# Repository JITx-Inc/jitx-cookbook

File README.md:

# The JITX Cookbook

Here you'll find a number of recipes (example projects) that will show you what JITX can do while serving as a base for your next project.

### How to Use

1. Install VSCode and JITX extension [How to install JITX](https://docs.jitx.com/faq/installationinstructions.html)
2. Open to root cookbook folder in VSCode with `File -> Open Folder -> (Select jitx-cookbook folder)`
3. Open `main.stanza` in the subfolder of the project that you want to run and press "Ctrl+Enter"

You've now built the recipe! Checkout the tutorial and documentation to learn more about JITX: [JITX Docs](https://docs.jitx.com/)

### Recipes

Click any of the links below to access a detailed walkthrough of how they were designed in JITX.

| Recipe                                                                 | What It Can Do                                                                                                                               |
| -------------                                                          | -------------                                                                                                                                |
| [Battery Charger](./battery_charger_design/)                           | LiPo battery charger, LDO voltage regulator, USB-C connector, JST battery connector, resistors, capacitors, detailed checks, export to KiCad |
| [USB-C Cable Tester](./usb_c_cable_tester/)                            | Test points, programmatic parts placement, USB-C connectors, LEDs, coin cell battery, circuit introspection                                  |
| [BLE-mote Wireless IOT Sensor Board](./ble_mote_esp32_iot_board/)      | Microcontroller, pin assignment (supports/requires), parametric design, design optimization, copper pour, net-classes, stackup               |
| [Hacking Conference Badge](./hacking_conference_badge/)                | A software-defined electronics playground - learn JITX by designing your own conference badge                                                |
| [Example of a reusable regulator design (TPS62933DRLR)](./regulator-example/) | Regulator fed from USB-C PD capable of delivering high current |
| [Example of a reusable keyboard layout generator](./keyboard/) | Keyboard generator which generates layout which is quickly implementable  |
| [Ambiq processor along with a few peripherals](./ambiq_demo/) | System based on Ambiq Apollo 4 Blue processor with wireless charging MIPI-DSI, octal SPI, 6-axis IMU peripherals which demonstrate pin assignment and SI constraints|
### What is a recipe?

These recipes are fully functional projects built in JITX to help show you what JITX can do, teach you how to do what you need in JITX, and to serve as reference or template projects for your next design. Recipes can be thought of as JITX example projects, reference designs, recipes, project blueprints, and/or design templates.

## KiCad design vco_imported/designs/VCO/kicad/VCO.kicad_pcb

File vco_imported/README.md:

# Voltage Controlled Oscillator Recipe

This tutorial guides you on importing a project from KiCad into JITX, modifying it, and exporting it back for production.

## The Project

This is a VCO made for a modular synthesizer in the eurorack standard. The original design is from [here](https://github.com/MatthewATaylor/Modular-Synth-Hardware/tree/main/VCO)

#### General Outline

In this project, we want to:

1. Import an existing KiCad from a GitHub repository
4. Change the board stackup to 4 layers and use JLCPCB rules
2. Change most through hole components to SMD components which are available from LCSC
4. Use a matched PNP transistor pair instead of the 2k tempco resistor with 2 separate PNP transistors
2. Export the design back to KiCad and simulate the output

## Getting Started

#### Prerequisites

To start, we'll need to setup JITX. We can follow this tutorial to get setup: https://docs-testing.jitx.com/faq/installationinstructions.html

Then, we need to clone the repo from which we're importing the design. We'll do this by running:
```
git clone https://github.com/MatthewATaylor/Modular-Synth-Hardware
```

Now we want to create a folder in which we'll have our JITX files. This can be done by using your operating system's file explorer.

#### Importing the design

First, let's open VSCode and make sure that no project is open. If there's a project open then we can start with no project by going to `File -> New Window` or using the keyboard shortcut `Ctrl+Shift+N`.

Next we open the JITX sidebar by clicking the small JITX logo to the side and then clicking "Import from Kicad"

Then we navigate to the folder where we cloned the repo to import from and then to the folder `VCO`. Delete the `Panel` folder or move it somewhere else since we currently don't want to import that project. Now select `VCO` and click `Choose as input directory`.

Select the new folder we made as the output directory. If the import was successful, your VSCode window should look like this:

The files generated are as follows:

```text
.
├── board.stanza                    The definition of the board shape, stackup, and rules
├── components                      Automatically generated component files for each unique component on the board
│   └── UNKNOWN
│       └── ... 
├── geometry.stanza                 The definition of each of the copper-filled layers and traces made previously on the board 
├── labels.stanza                   The silkscreens of components and their location
├── landpatterns                    The landpatterns of automatically generated components
│   └── ...
├── log.txt                         The log containing errors and warnings during the import process
├── placements.stanza               Contains the fixed location at which each component is placed
├── properties.stanza               Contains properties automatically generated for each component
├── reference-designators.stanza    Contains the name of each component as shown on the board
├── run-design.stanza               Helper functions to build, check, and export the design
├── stanza.proj                     Contains the locations of libraries that are imported into the project
├── symbols                         Contains the symbols used for the schematic
│   └── ... 
└── VCO.stanza                      Main file containing the instantiation of components and their connections
```

## Main Design

First, we want to remove the existing trace geometry since we want to make our own using the autorouter. We can do this by removing or commenting out the following line in `VCO.stanza`:
```
add-main-geometry()
```

Let's also define our 4 copper layers, the current stackup is:
```text
==GND==
==+12==
==-12==
==GND==
```
We have +12V and -12V as nets since we're receiving a bipolar power supply.

We also want to increase the size of our power traces so we will make a `NetClass` for that.

Now, we want to change our stackup and rules. We'll go to `board.stanza` and change the stackup to a 4 layer board from JLCPCB which is available in the OCDB.

We want a larger default trace too so we can copy the JLCPCB rules from `ocdb/manufacturers/rules.stanza` and change `min-copper-width` to `0.25`

In `run-design.stanza`, change `export-design()` to `compile-design(main)` so that when we run `ctrl+enter` inside, we can view the board and schematic

#### Replacing passive components

Next, we want to change out our generic components to something available from LCSC which is also an SMD component. We'll move to `VCO.stanza` and switch out our resistors and capacitors. We don't have to explicitly define values for each component and instead we can take the value from the `emodel` (electrical model) of our component. Here we made 2 functions to convert our components with emodels to resistors or capacitors:
```
public defn emodel2resistor (component:Instantiable -- extraparams:Tuple = []) :
  chip-resistor(to-tuple(cat(["resistance" => resistance(emodel?(component) as Resistor) as Double], extraparams)))

public defn emodel2capacitor (component:Instantiable -- extraparams:Tuple = []) :
  ceramic-cap(to-tuple(cat(["capacitance" =>capacitance(emodel?(component) as Capacitor) as Double], extraparams)))
```

Now we can change all the instantiations of resistors with a well written find-and-replace command (`ctrl+h`):
```
Find: VCO/components/UNKNOWN/R(-?[0-9]*)/component
Replace: emodel2resistor(VCO/components/UNKNOWN/R$1/component, extraparams = ["_exist" => ["vendor_part_numbers.lcsc"]])
```
Don't forget to turn on regular expressions using `alt+r`

Since these resistors are not 0 indexed, we have to change the net statements to use p[2] instead of p[0]. This can be done again with find-and-replace.
```
Find: R(-?[0-9]*).p\[0\]
Replace: R$1.p[2]
```

The same can be done with capacitors

Some of our capacitors are better as film capacitors since they are less microphonic and more linear so we will replace those with film capacitors from a database part query
```
public inst jitx-C-3 :  database-part(["mpn" => "ECHU1C102GX5", "manufacturer" => "Panasonic"])
```

#### Replacing other components

Instead of the 2 2n3906 transistors and 2k tempco resistor used, we want to use a matched PNP pair. Thus, we will remove the instantiations in `VCO.stanza` (the tempco is R-64), placements in `placements.stanza`, reference designators in `reference-designators.stanza`, and `ref-labels` and `value-labels` in `labels.stanza`

Then we can instantiate the matched pair (we're using an mmdt3906) using the database part query and change the original 2n3906 pins to mmdt3906 pins. The tempco resistor's net statements should be removed.
```
public inst mmdt3906 : database-part(["mpn" => "MMDT3906", "manufacturer" => "Jiangsu Changjing Electronics Technology Co., Ltd."])
```

Now we can change the rest of the components to part queries. Components can be found using the Component Search available in JITX. This can be found by going to the JITX sidebar and clicking "Explorer".

It's best to find components that have the same or similar pin names as the names don't have to be replaced in the nets. Alternatively, you can change the component definition by clicking on a component definition while holding `ctrl`, and changing the `pcb-component` to a `pcb-module` and use that format. 

Before:
```
public pcb-component component :
  datasheet = "http://www.ti.com/lit/ds/symlink/tl071.pdf"
  pin-properties :
    [pin:Ref | pads:Ref ... | side:Dir | bank:Ref | electrical-type:String]
    [p[0] | p[1] | Right | A | "Output"]
    [p-[0] | p[2] | Left | A | "Input"]
    [p+[0] | p[3] | Left | A | "Input"]
    [p+[1] | p[5] | Left | B | "Input"]
    [p-[1] | p[6] | Left | B | "Input"]
    [p[1] | p[7] | Right | B | "Output"]
    [V- | p[4] | Down | C | "PowerIn"]
    [V+ | p[8] | Up | C | "PowerIn"]

  assign-landpattern(VCO/landpatterns/DIP-8_W762mm_Socket/DIP-8_W762mm_Socket)
  assign-symbols([
    Ref("A") => TL072A
    Ref("B") => TL072B
    Ref("C") => TL072C
  ])
```

After:
```
public pcb-module component :
  port p : pin[2]
  port p- : pin[2]
  port p+ : pin[2]
  pin V-
  pin V+

  val datasheet = "http://www.ti.com/lit/ds/symlink/tl071.pdf"

  inst tl072 : database-part(["mpn" => "TL072CDT", "manufacturer" => "STMicroelectronics"])

  net (p[0] tl072.P_1OUT)
  net (p[1] tl072.P_2OUT)
  net (p-[0] tl072.P_1IN-)
  net (p-[1] tl072.P_2IN-)
  net (p+[0] tl072.P_1IN+)
  net (p+[1] tl072.P_2IN+)
  net (V- tl072.VCC-)
  net (V+ tl072.VCC+)
```

Note that you need to delete the reference designator for this component in `reference-designators.stanza` after doing this or explicitly choosing the instantiation in the `pcb-module` (`self.TL072-1.tl072` for example). The placement is also lost this way.

## Layout + Order

#### Layout
With all our components and connections defined, now we can place our components where we want on the board. Then we can select pads (`shift+click`) or select whole pads (press `a`) and then press `q` to route traces through those pads. We can use vias where necessary by pressing `v` and then dragging from a pad.

If components are out of place, then change the location and orientation in `placements.stanza` or remove their placement and move them by dragging them around. Components can be rotated by pressing `r`. Note that component placements can't be changed if they're explicitly defined.

#### Export to KiCad

Now that we're happy with the layout, we can export the design straight into KiCad.

First, let's go into `helpers.stanza`, set KiCad as our CAD tool, and add a mapping so that the custom LCSC field get's exported with our components:
```
val export-field-mapping = [
  "LCSC" => "LCSC"
  "lcsc" => "LCSC"
  "vendor_part_numbers.lcsc" => "LCSC"
]
defn export-to-cad () :
  set-paper(ANSI-A4)
  set-export-backend(`kicad)
  export-cad(export-field-mapping)
```
Then we build the project with `Ctrl + Enter`, and export with `export-design()` in our REPL (terminal), and a KiCad project is generated in the "CAD" directory.

#### Finishing touches in KiCad 

Let's open up KiCad, open the project, and open the schematic + board viewers. The first thing to do is to click the "Update PCB with changes made to schematic" button in the board view to ensure everything has synced.

Then, change the silkscreen position and add vias as deemed necessary.

A SPICE simulation can also be done in the schematic viewer of KiCad to test the circuit (this requires some setting up).

## Conclusion

We've now successfully imported and redesigned a PCB using JITX. You can use this as a reference project, copying this workflow to design your own systems. To learn more, check out the other recipes in [the JITX Cookbook Recipes repo](https://github.com/JITx-Inc/jitx-cookbook) and read through the [tutorials](https://docs.jitx.com/tutorials/index.html) in the JITX docs.

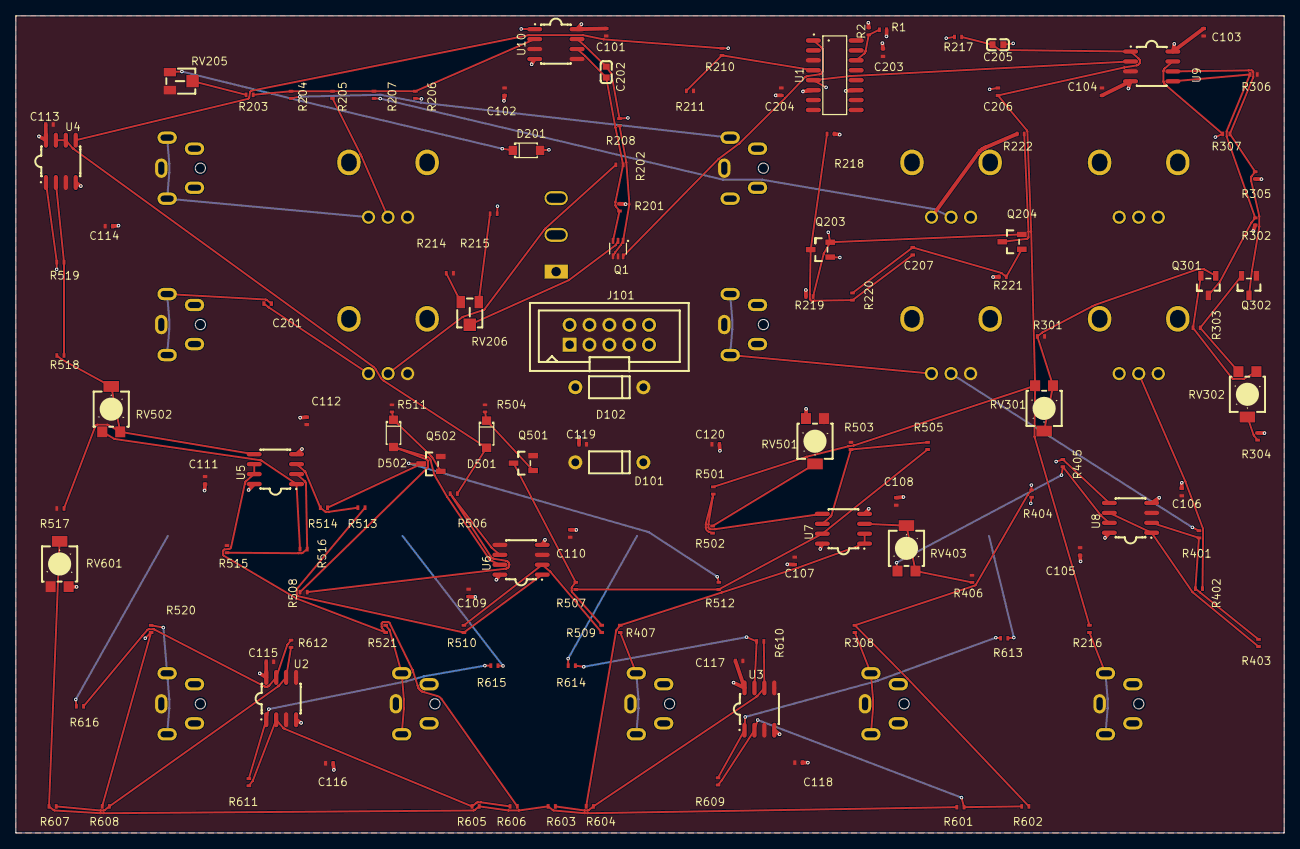
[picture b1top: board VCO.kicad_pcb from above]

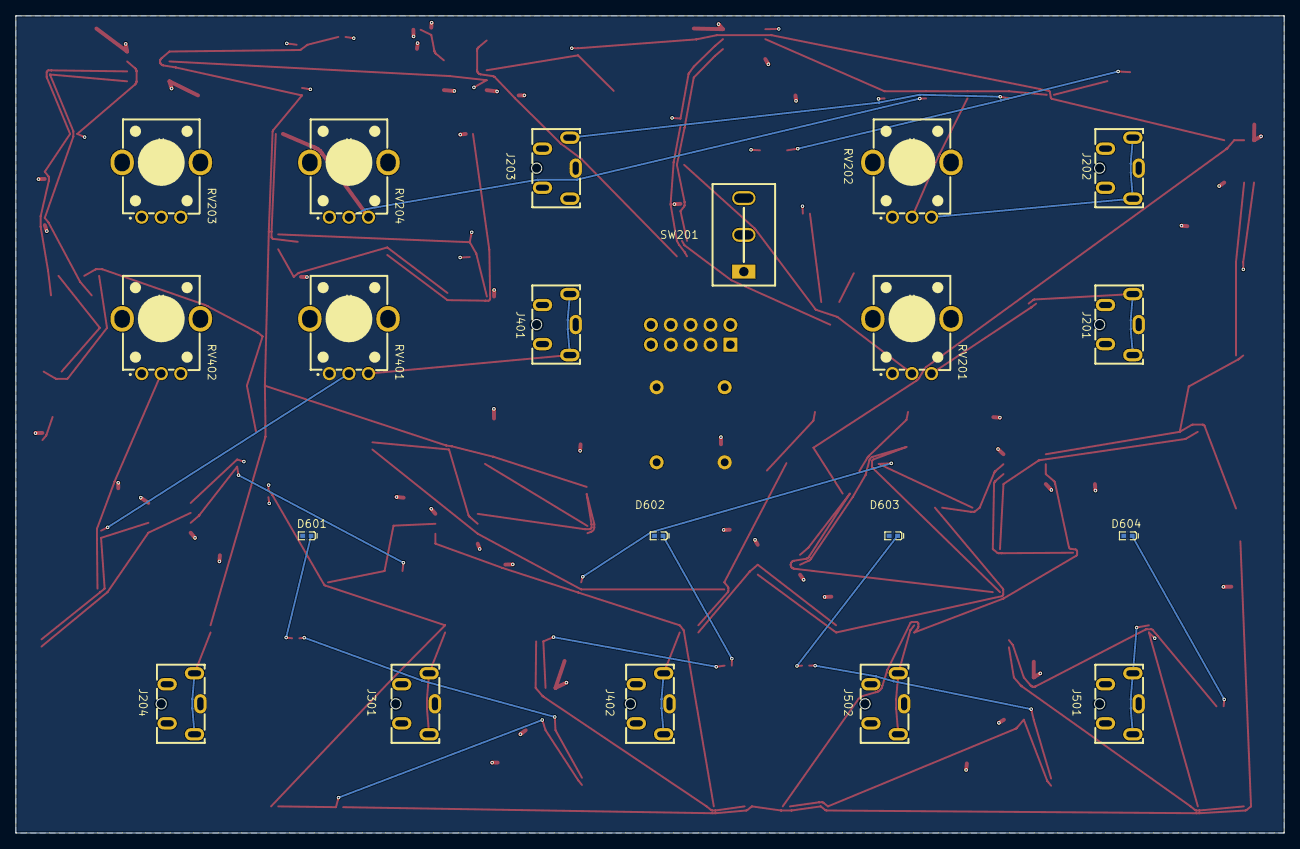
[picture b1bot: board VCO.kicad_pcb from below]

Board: 4 copper layers, 162.2 x 104.5 mm, 151 parts (20 on the bottom side), 87 nets.

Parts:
C101, C102, C103, C104, C105, C106, C107, C108, C109, C110, C111, C112, C113, C114, C115, C116, C117, C118, C203, C204, C206: 10n; Pkg0402_2
C119, C120: 100n; Pkg0402_2
C201: 220n; Pkg0402_2
C202: 1n; C0603_1
C205: 1n; C0603
C207: 47p; Pkg0402_2
D101: 1N5819; DO_41_BD2_4_L4_7_P8_70_D0_9_FD_1
D102: 1N5819; DO_41_BD2_4_L4_7_P8_70_D0_9_FD
D201: 1N4148; SOD_123_L2_7_W1_6_LS3_8_RD
D501: 1N4148; SOD_123_L2_7_W1_6_LS3_8_RD_2
D502: 1N4148; SOD_123_L2_7_W1_6_LS3_8_RD_1
D601: LED; LED0402_RD_3
D602: LED; LED0402_RD_2
D603: LED; LED0402_RD_1
D604: LED; LED0402_RD
J101: Conn_02x05_Odd_Even; IDC_TH_10P_P2_54_V_R2_C5_S2_54
J201: AudioJack2_SwitchT; AUDIO_TH_PJ_3582_B
J202: AudioJack2_SwitchT; AUDIO_TH_PJ_3582_B_5
J203: AudioJack2_SwitchT; AUDIO_TH_PJ_3582_B_2
J204: AudioJack2_SwitchT; AUDIO_TH_PJ_3582_B_7
J301: AudioJack2_SwitchT; AUDIO_TH_PJ_3582_B_3
J401: AudioJack2_SwitchT; AUDIO_TH_PJ_3582_B_8
J402: AudioJack2_SwitchT; AUDIO_TH_PJ_3582_B_4
J501: AudioJack2_SwitchT; AUDIO_TH_PJ_3582_B_1
J502: AudioJack2_SwitchT; AUDIO_TH_PJ_3582_B_6
Q1: MMDT3906; SOT_363_L2_0_W1_3_P0_65_LS2_1_BL
Q203: 2N3904; SOT_23_3_L2_9_W1_3_P1_90_LS2_4_TR
Q204: 2N3904; SOT_23_3_L2_9_W1_3_P1_90_LS2_4_TR_4
Q301: 2N3904; SOT_23_3_L2_9_W1_3_P1_90_LS2_4_TR_3
Q302: 2N3904; SOT_23_3_L2_9_W1_3_P1_90_LS2_4_TR_2
Q501: 2N3904; SOT_23_3_L2_9_W1_3_P1_90_LS2_4_TR_1
Q502: 2N3904; SOT_23_3_L2_9_W1_3_P1_90_LS2_4_TR_5
R1, R2, R211, R302, R305, R517: 10K; Pkg0402
R201: 1M5; Pkg0402
R202, R501, R502, R503, R505: 6K8; Pkg0402
R203: 2M2; Pkg0402_1
R204, R205, R206, R210, R504, R511: 100K; Pkg0402_1
R207: 3M3; Pkg0402
R208, R220: 22K; Pkg0402
R214: 820R; Pkg0402
R215: 47R; Pkg0402_1
R216, R308, R407, R520, R521: 1K; Pkg0402
R217: 1M; Pkg0402
R218: 180K; Pkg0402
R219, R613, R614, R615, R616: 75K; Pkg0402
R221: 560K; Pkg0402
R222: 33K; Pkg0402_1
R301: 220R; Pkg0402
R303: 330R; Pkg0402
R304: 15K; Pkg0402
R306, R307, R506, R508, R509, R510: 7K5; Pkg0402
R401, R403: 150K; Pkg0402
R402: 330K; Pkg0402
R404, R406: 2K2; Pkg0402_1
R405: 2M; Pkg0402
R507, R512: 1K5; Pkg0402_1
R513, R514, R515, R516: 3K9; Pkg0402
R518, R519, R601, R602, R603, R604, R605, R606, R607, R608, R609, R610, R611, R612: 680K; Pkg0402
RV201: 50K; RES_TH_RK09K1130AAU
RV202: 50K; RES_TH_RK09K1130AAU_3
RV203: 50K; RES_TH_RK09K1130AAU_1
RV204: 50K; RES_TH_RK09K1130AAU_4
RV205: 100K; RES_ADJ_SMD_3313J_1_1
RV206: 100R; RES_ADJ_SMD_3313J_1
RV301: 10K; RES_ADJ_SMD_3314G_1_103E_4
RV302: 10K; RES_ADJ_SMD_3314G_1_103E_2
RV401: 50K; RES_TH_RK09K1130AAU_2
RV402: 50K; RES_TH_RK09K1130AAU_5
RV403: 10K; RES_ADJ_SMD_3314G_1_103E
RV501: 10K; RES_ADJ_SMD_3314G_1_103E_3
RV502: 10K; RES_ADJ_SMD_3314G_1_103E_1
RV601: 10K; RES_ADJ_SMD_3314G_1_103E_5
SW201: SW_SPDT; SW_TH_MT_0_103_A101_M200_RS
U1: LM13700MNOPB; SOIC_16_L9_9_W3_9_P1_27_LS6_0_BL
U2, U3, U4, U5, U6, U7, U8, U9, U10: TL072CDT; SOIC_8_L5_0_W4_0_P1_27_LS6_0_BL

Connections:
/2: TL072-8_tl072/Net-J204-PadT: J204.3, J204.6, R216.2
/2: TL072-8_tl072/Net-J301-PadT: J301.3, J301.6, R308.2
/2: TL072-8_tl072/Net-Q301-Pad1: Q301.1 (E), R303.1, RV302.3
/2: TL072-8_tl072/Net-Q301-Pad3: Q301.3 (C), R302.2, R306.2, U9.5 (P_2IN+)
/2: TL072-8_tl072/Net-Q302-Pad1: Q302.1 (E), R303.2, RV302.1
/2: TL072-8_tl072/Net-Q302-Pad3: Q302.3 (C), R305.2, R307.1, U9.6 (P_2IN-)
/2: TL072-8_tl072/Net-R304-Pad1: R304.1, RV302.2
/3: TL072-9_tl072/LEDPulse: R407.2, R604.2, U7.1 (P_1OUT), U7.2 (P_1IN-)
/3: TL072-9_tl072/Net-D201-Pad1: D201.1 (K), RV205.3
/3: TL072-9_tl072/Net-D601-Pad1: D601.1 (K), R613.1
/3: TL072-9_tl072/Net-D602-Pad1: D602.1 (K), R614.1
/3: TL072-9_tl072/Net-J203-PadT: J203.3, J203.6, R204.1
/3: TL072-9_tl072/Net-J402-PadT: J402.3, J402.6, R407.1
/3: TL072-9_tl072/Net-R203-Pad1: R203.1, RV205.2
/3: TL072-9_tl072/Net-R207-Pad1: R207.1, RV204.2
/3: TL072-9_tl072/Net-R502-Pad1: R502.1, RV501.2
/3: TL072-9_tl072/Net-R601-Pad1: R601.1, R602.1, R609.2, U3.2 (P_1IN-)
/3: TL072-9_tl072/Net-R603-Pad1: R603.1, R604.1, R610.2, U3.6 (P_2IN-)
/3: TL072-9_tl072/Net-R609-Pad1: R609.1, R613.2, U3.1 (P_1OUT)
/3: TL072-9_tl072/Net-R610-Pad1: R610.1, R614.2, U3.7 (P_2OUT)
/4: TL072-7_tl072/Net-C207-Pad1: C207.1, Q203.3 (C), R218.2, R220.1
/4: TL072-7_tl072/Net-C207-Pad2: C207.2, Q204.2 (B), R220.2, R221.1
/4: TL072-7_tl072/Net-D501-Pad1: D501.1 (K), Q501.2 (B), R504.2
/4: TL072-7_tl072/Net-D603-Pad1: D603.1 (K), R615.1
/4: TL072-7_tl072/Net-D604-Pad1: D604.1 (K), R616.1
/4: TL072-7_tl072/Net-J502-PadT: J502.3, J502.6, R521.1
/4: TL072-7_tl072/Net-Q203-Pad2: Q203.2 (B), R217.2
/4: TL072-7_tl072/Net-Q204-Pad3: Q204.3 (C), R222.2
/4: TL072-7_tl072/Net-R206-Pad1: R206.1, RV203.2
/4: TL072-7_tl072/Net-R402-Pad1: R402.1, RV402.2
/4: TL072-7_tl072/Net-R403-Pad2: R403.2, U8.1 (P_1OUT), U8.6 (P_2IN-)
/4: TL072-7_tl072/Net-R405-Pad2: R405.2, RV403.3, U8.7 (P_2OUT)
/4: TL072-7_tl072/Net-R605-Pad1: R605.1, R606.1, R611.2, U2.2 (P_1IN-)
/4: TL072-7_tl072/Net-R607-Pad1: R607.1, R608.1, R612.2, U2.6 (P_2IN-)
/4: TL072-7_tl072/Net-R611-Pad1: R611.1, R615.2, U2.1 (P_1OUT)
/4: TL072-7_tl072/Net-R612-Pad1: R612.1, R616.2, U2.7 (P_2OUT)
/5: TL072-4_tl072/Net-D502-Pad1: D502.1 (K), Q502.2 (B), R511.2
/5: TL072-4_tl072/Net-D502-Pad2: D502.2 (A), R508.2, U6.7 (P_2OUT)
/5: TL072-4_tl072/Net-J401-PadT: J401.3, J401.6, RV401.3
/5: TL072-4_tl072/Net-J501-PadT: J501.3, J501.6, R520.1
/5: TL072-4_tl072/Net-Q502-Pad3: Q502.3 (C), R512.1, R514.1
/5: TL072-4_tl072/Net-R401-Pad1: R401.1, RV401.2
/5: TL072-4_tl072/Net-R506-Pad2: R506.2, R508.1, U6.6 (P_2IN-)
/5: TL072-4_tl072/Net-R509-Pad2: R509.2, R510.1, U6.2 (P_1IN-)
/5: TL072-4_tl072/Net-R510-Pad2: R510.2, R513.1, U6.1 (P_1OUT)
/5: TL072-4_tl072/Net-R513-Pad2: R513.2, R514.2, U5.3 (P_1IN+)
/5: TL072-4_tl072/Net-R515-Pad2: R515.2, R516.1, U5.2 (P_1IN-)
/5: TL072-4_tl072/Net-R516-Pad2: R516.2, RV502.3, U5.1 (P_1OUT)
/5: TL072-4_tl072/Net-R517-Pad2: R517.2, R518.2, RV502.1, RV502.2, U5.5 (P_2IN+)
/5: TL072-4_tl072/Net-R518-Pad1: R518.1, R519.2, U4.2 (P_1IN-)
/6: CA3080_lm13700/Net-C201-Pad1: C201.1, J201.3, J201.6
/6: CA3080_lm13700/Net-C201-Pad2: C201.2, RV201.3
/6: CA3080_lm13700/Net-C205-Pad1: C205.1, SW201.1
/6: CA3080_lm13700/Net-C206-Pad1: C206.1, SW201.3
/6: CA3080_lm13700/Net-J202-PadT: J202.3, J202.6, RV202.3
/6: CA3080_lm13700/Net-R202-Pad1: R202.1, RV201.2
/6: CA3080_lm13700/Net-R205-Pad1: R205.1, RV202.2
/6: CA3080_lm13700/Net-R210-Pad2: R210.2, R211.1, U1.4 (Input-0)
/7: R_Potentiometer_Trim-7/Net-R214-Pad1: R214.1, RV206.1
/7: R_Potentiometer_Trim-7/Net-R215-Pad2: R215.2, RV206.3
BaseSquare: Q203.1 (E), Q204.1 (E), R210.1, R219.1, U4.5 (P_2IN+)
BaseTriangle: C205.2, C206.2, R216.1, R217.1, R501.1, RV301.1, U9.1 (P_1OUT)
GND: C101.2, C102.2, C103.2, C104.2, C105.2, C106.2, C107.2, C108.2, C109.2, C110.2, C111.2, C112.2, C113.2, C114.2, C115.2, C116.2, C117.2, C118.2, C119.2, C120.1, C203.2, C204.2, D101.1 (A), D102.2 (K), D601.2 (A), D602.2 (A), D603.2 (A), D604.2 (A), J101.3, J101.4, J101.5, J101.6, J101.7, J101.8, J201.2, J202.2, J203.2, J204.2, J301.2, J401.2, J402.2, J501.2, J502.2, Q1.5 (B2), Q302.2 (B), Q501.1 (E), Q502.1 (E), R211.2, R214.2, R301.2, R306.1, R406.1, R503.1, R504.1, R511.1, R515.1, R517.1, RV201.1, RV202.1, RV205.1, RV401.1, RV501.3, RV601.3, U1.3 (Input+0), U2.3 (P_1IN+), U2.5 (P_2IN+), U3.3 (P_1IN+), U3.5 (P_2IN+), U4.3 (P_1IN+), U6.3 (P_1IN+), U6.5 (P_2IN+), U8.3 (P_1IN+), U9.3 (P_1IN+), U10.3 (P_1IN+), U10.5 (P_2IN+)
LEDInvertedSaw: R519.1, R520.2, R608.2, U4.1 (P_1OUT)
LEDSaw: R521.2, R606.2, U5.6 (P_2IN-), U5.7 (P_2OUT)
LEDSine: R307.2, R308.1, R404.2, R602.2, U9.7 (P_2OUT)
Net+12V: C101.1, C103.1, C105.1, C107.1, C109.1, C111.1, C113.1, C115.1, C117.1, C119.1, C203.1, D101.2 (K), J101.1, J101.2, R1.1, R218.1, R222.1, R302.1, R305.1, RV203.3, RV204.3, RV402.3, RV501.1, RV601.1, U1.11 (V+), U2.8 (VCC+), U3.8 (VCC+), U4.8 (VCC+), U5.8 (VCC+), U6.8 (VCC+), U7.8 (VCC+), U8.8 (VCC+), U9.8 (VCC+), U10.8 (VCC+)
Net-12V: C102.1, C104.1, C106.1, C108.1, C110.1, C112.1, C114.1, C116.1, C118.1, C120.2, C204.1, D102.1 (A), J101.9, J101.10, R2.2, R201.1, R219.2, R221.2, R304.2, RV203.1, RV204.1, RV402.1, U1.6 (V-), U2.4 (VCC-), U3.4 (VCC-), U4.4 (VCC-), U5.4 (VCC-), U6.4 (VCC-), U7.4 (VCC-), U8.4 (VCC-), U9.4 (VCC-), U10.4 (VCC-)
unnamed: R1.2, R2.1, U1.14 (Input+1)
Net-C202-Pad1: C202.1, Q1.3 (C2), R201.2, R202.2, U10.6 (P_2IN-)
Net-C202-Pad2: C202.2, D201.2 (A), R208.2, U10.7 (P_2OUT)
Net-D501-Pad2: D501.2 (A), R506.1, U4.6 (P_2IN-), U4.7 (P_2OUT)
Net-Q201-Pad1: Q1.1 (E1), Q1.4 (E2), R208.1
Net-Q202-Pad2: Q1.2 (B1), RV206.2
Net-Q202-Pad3: Q1.6 (C1), U1.1 (Amp_bias_input0)
Net-Q301-Pad2: Q301.2 (B), R301.1, RV301.2, RV301.3
Net-Q501-Pad3: Q501.3 (C), R507.1, R509.1
Net-R203-Pad2: R203.2, R204.2, R205.2, R206.2, R207.2, U10.2 (P_1IN-)
Net-R209-Pad2: R215.1, U10.1 (P_1OUT)
Net-R401-Pad2: R401.2, R402.2, R403.1, U8.2 (P_1IN-)
Net-R404-Pad1: R404.1, R405.1, U8.5 (P_2IN+)
Net-R406-Pad2: R406.2, RV403.1, RV403.2, U7.3 (P_1IN+)
Net-R501-Pad2: R501.2, R502.2, U7.5 (P_2IN+)
Net-R503-Pad2: R503.2, R505.1, U7.6 (P_2IN-)
Net-R505-Pad2: R505.2, R507.2, R512.2, U7.7 (P_2OUT)
Net-R601-Pad2: R601.2, R603.2, R605.2, R607.2, RV601.2
Net-SW201-Pad2: SW201.2, U1.5 (Output0), U9.2 (P_1IN-)

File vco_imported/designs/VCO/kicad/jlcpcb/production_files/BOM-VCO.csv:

Comment,Designator,Footprint,LCSC
100R,RV206,RES_ADJ_SMD_3313J_1,C124614
LED,"D601,D602,D603,D604",LED0402_RD_3,C130719
LM13700MNOPB,U1,SOIC_16_L9_9_W3_9_P1_27_LS6_0_BL,C1346265
220n,C201,Pkg0402_2,C16772
1n,"C202,C205",C0603_1,C178413
SW_SPDT,SW201,SW_TH_MT_0_103_A101_M200_RS,C1788493
2N3904,"Q203,Q204,Q301,Q302,Q501,Q502",SOT_23_3_L2_9_W1_3_P1_90_LS2_4_TR,C18536
2K2,"R404,R406",Pkg0402_1,C1857667
MMDT3906,Q1,SOT_363_L2_0_W1_3_P0_65_LS2_1_BL,C20534
100K,"R204,R205,R206,R210,R504,R511",Pkg0402_1,C2075193
2M2,R203,Pkg0402_1,C2076597
1M5,R201,Pkg0402,C2082545
1M,R217,Pkg0402,C2085938
3K9,"R513,R514,R515,R516",Pkg0402,C2086763
330R,R303,Pkg0402,C2097621
100n,"C119,C120",Pkg0402_2,C2168180
1N5819,"D101,D102",DO_41_BD2_4_L4_7_P8_70_D0_9_FD_1,C2474
10K,"R1,R2,R211,R302,R305,R517",Pkg0402,C2838653
10n,"C101,C102,C103,C104,C105,C106,C107,C108,C109,C110,C111,C112,C113,C114,C115,C116,C117,C118,C203,C204,C206",Pkg0402_2,C318577
1K,"R216,R308,R407,R520,R521",Pkg0402,C3972394
560K,R221,Pkg0402,C3999808
820R,R214,Pkg0402,C4062103
22K,"R208,R220",Pkg0402,C4062114
680K,"R518,R519,R601,R602,R603,R604,R605,R606,R607,R608,R609,R610,R611,R612",Pkg0402,C4075524
180K,R218,Pkg0402,C4078042
3M3,R207,Pkg0402,C4080317
6K8,"R202,R501,R502,R503,R505",Pkg0402,C4156192
7K5,"R306,R307,R506,R508,R509,R510",Pkg0402,C4156241
2M,R405,Pkg0402,C4156295
220R,R301,Pkg0402,C4165539
75K,"R219,R613,R614,R615,R616",Pkg0402,C4266729
1K5,"R507,R512",Pkg0402_1,C4268869
150K,"R401,R403",Pkg0402,C4288097
Conn_02x05_Odd_Even,J101,IDC_TH_10P_P2_54_V_R2_C5_S2_54,C429962
330K,R402,Pkg0402,C4333841
50K,"RV201,RV202,RV203,RV204,RV401,RV402",RES_TH_RK09K1130AAU,C470291
AudioJack2_SwitchT,"J201,J202,J203,J204,J301,J401,J402,J501,J502",AUDIO_TH_PJ_3582_B,C500090
15K,R304,Pkg0402,C593362
TL072CDT,"U10,U2,U3,U4,U5,U6,U7,U8,U9",SOIC_8_L5_0_W4_0_P1_27_LS6_0_BL,C6961
10K,"RV301,RV302,RV403,RV501,RV502,RV601",RES_ADJ_SMD_3314G_1_103E_4,C780220
47R,R215,Pkg0402_1,C852803
33K,R222,Pkg0402_1,C853915
47p,C207,Pkg0402_2,C882562
100K,RV205,RES_ADJ_SMD_3313J_1_1,C89235
1N4148,"D201,D501,D502",SOD_123_L2_7_W1_6_LS3_8_RD,C909967

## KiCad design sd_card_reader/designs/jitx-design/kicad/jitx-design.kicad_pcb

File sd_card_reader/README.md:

# SD Card Reader Cookbook Recipe
This tutorial guides you on creating an SD Card Reader using JITX while highlighting different features that can be used to aid users on their designs.

##  The Project
This is an SD card reader built in a small form factor, designed to fit in the framework laptop (untested).

## Getting Started
#### Prerequisites
To start, we'll need to setup JITX. We can follow this tutorial to get setup: https://docs-testing.jitx.com/faq/installationinstructions.html

Then, we need to create a new project. So let's run VSCode, select the JITX extension, and click "New Project".

Now we're ready to start designing the board.

> NOTE: The code below is not the entire design. Refer to the [Github repo](https://github.com/JITx-Inc/jitx-cookbook/tree/main/sd_card_reader) for a full working design. Below, we describe the design flow and thought process behind designing this board.

#### Intended Functionality
We want our design to be able to:

* Read and write from an SD Card
* Interface with a computer using a USB-C male connector
* Show the status of data transfer with an LED
* Enable USB device customization using an EEPROM
#### Implementation Plan
To accomplish this, we will use:

* A controller: Microchip USB2240-AEZG-06
* A power regulator: ROHM Semicon BD433M5FP-CE2
* An EEPROM: ST Microelectronics M24C04-WMN6TP
* A USB C male connector: HRO Electronics TYPE-C-31-G-03 
* An SD card connector: XUNPU SD-101 
* Miscellaneous generic components

## Components
Most of our main components (like our controller) don't exist in the OCDB so we will define these ourselves. Fortunately, we don't have to build the landpattern definitions and pin definitions as our parts exist in the parts database. 

We can look for parts using the component search. Since, we want to manufacture this board from JLCPCB, we should look for components that have the property `vendor_part_numbers.lcsc`.

We want to define each of our main components in their own separate modules so we can reuse them later on for different projects. Thus, each component is put into a `pcb-module`.

#### Microcontroller
For this project, we're going to use a Microchip USB2240. For each module we're going to follow a workflow:

* See what inputs and outputs we want and define them as pins and ports. 
    * We want to use bundles (ports) for pins that are commonly connected together. We can look for bundles in the OCDB by opening `ocdb/utils/bundles.stanza` 
```
port power : power
port i2c : i2c
port usb-in : usb-2
port sd-card-conn : sd-card-uhs-1-connector
pin LED
```
* We can also create our own bundles if they don't exist in the OCDB. `sd-card-uhs-1-connector` is an example
```
public pcb-bundle sd-card-uhs-1-connector:
  pin CMD ; Command/Response
  port power : power ; 3.3v and 2 ground pins
  pin CLK ; Clock
  port DAT : pin[4] ; Data pins (last pin also used as card detect)
  pin CD ; Card detect
  pin WP ; Write protect
```

* Instantiate the exact part we want using a database part query
    * An alternative to making a query could be searching for this part in the component search and clicking "Create component" after selecting a suitable component.
```
inst usb2240 : database-part(["manufacturer" => "Microchip", "mpn" => "USB2240-AEZG-06"])
```

* Go through the pins using the design explorer (you can find this by opening the sidebar and clicking "Explorer" under the "Views" section)
* Define each pin's properties with the help of the part's datasheet and the [JITX documentation](https://docs.jitx.com/reference/utilities/properties.html)
* Create and connect components that would be consistent for every use case for this design (pull-up resistors and decoupling capacitors etc.)
    * For this design, we always need a 24MHz crystal so we define it with the same workflow
    * `bypass-cap-strap` creates a capacitor which uses `short-trace`. The `short-trace` is a hint to the layout that we want our PCB trace to be as short as possible between both pads
    * It's best to define pins we're not using as a `no-connect` to avoid ERC errors in the design flow
    * The parameter `"_exist" => ["vendor_part_numbers.lcsc"]` allows us to specify that we require the part to have an LCSC number 

#### USB C male connector
Our application uses USB2 so we want to use the USB2 protocol over the USB-C connection. One key aspect of the backwards compatibility is to indicate device type using resistors on the CC1, CC2 pins. In this case, we need a pull-down resistor on the CC1 pin.

## Bundles
Bundles allow us to define a set of pins which are commonly used together and allow us to view the design at a higher level. Bundles also make connecting pins easy and foolproof. For example, we can create a bundle called `sd-card-uhs-1-connector` and define every pin required for an SD card. Now we can use this to connect our controller to the SD Card connector within a single `net` statement.

We can create bundles within bundles too to further simplify our code.

## Main Design 

We want to define a custom shape for our board with 5mm x 2mm notches so we create the board using a Polygon shape:
```
val board-shape = Polygon([Point(-15.0,-15.0), Point(10.0,-15.0), Point(10.0,-13.0), Point(15.0,-13.0), Point(15.0, 13.0), Point(10.0, 13.0), Point(10.0, 15.0), Point(-15.0,15.0)])
```

We also can to use this same shape for our ground copper ground planes which extend from edge to edge.
```
geom(gnd) :
    copper-pour(LayerIndex(0), isolate = 0.1, rank = 1, orphans = true) = board-shape
    copper-pour(LayerIndex(1), isolate = 0.1, rank = 1, orphans = true) = board-shape
```

Now that all our components and the board are defined, we can move on to placing and connecting our modules together. We use the `dims` function to get the dimensions of our custom board shape and use it for placement. 
```
val d = dims(board-shape)
```

Now we instantiate all our modules and also create testpoints which would allow us to update information on our EEPROM.
```
inst logo : ocdb/artwork/jitx-logo/logo(5.0)

; Call all our modules
inst usb : usb-2-on-usb-c-male
place(usb) at loc(x(d) / 2.0 + 1.1, 0.0, -270.0) on Bottom

inst reg : voltage-regulator

inst eeprom : eeprom

val testpoints = add-testpoint([eeprom.power.vdd eeprom.power.gnd eeprom.i2c.sda eeprom.i2c.scl], Testpoint-SMDPad)

inst media-controller : media-controller
place(media-controller) at loc(0.0, 0.0, 0.0) on Top

inst sd-connector : sd-connector
place(sd-connector) at loc(-5.0, 0.0, 270.0) on Bottom
```

We're reusing the LED circuit generator used in the [USB C cable tester](https://github.com/JITx-Inc/jitx-cookbook/tree/main/usb_c_cable_tester) to create our status LED. 
```
inst status-led : components/LED-maker-ROYGB/module(components/LED-maker-ROYGB/RED, property(vdd33.voltage))
```

Connecting our ports is easy now since we can net whole bundles together.
```
net (usb.usb-2.vbus reg.power-in)
net (usb.usb-2 media-controller.usb-in)

net (reg.power-out media-controller.power eeprom.power)

net (media-controller.i2c eeprom.i2c)
net (media-controller.sd-card-conn sd-connector.conn)

net (media-controller.LED status-led.in)
net (status-led.out gnd)
```

`check-design` allows us to use checks already made in the OCDB and use it for our board. 

## Layout + Order

#### Layout

With all our components and connections defined, now we can place our components where we want on the board. Then we can select single pads (`click`), extend the selection of pads (`shift+click`) or select all pads connected to the pad we first selected (press `a`) and then press `q` to route traces through those pads.

#### Export to KiCad

Now that we're happy with the layout, we can export the design straight into KiCad.

First, let's go into `helpers.stanza`, set KiCad as our CAD tool, and add a mapping so that the custom LCSC field gets exported as a component property:
```
val export-field-mapping = [
  "LCSC" => "LCSC"
  "lcsc" => "LCSC"
  "vendor_part_numbers.lcsc" => "LCSC"
]
defn export-to-cad () :
  set-paper(ANSI-A4)
  set-export-backend(`kicad)
  export-cad(export-field-mapping)
```
Then we build the project with `Ctrl + Enter`, and export with `export-design()` in our REPL (terminal), and a KiCad project is generated in the "CAD" directory.

#### Finishing touches in KiCad 

Let's open up KiCad, open the project, and open the schematic + board viewers. The first thing to do is to click the "Update PCB with changes made to schematic" button in the board view to ensure everything has synced.

Then we need to change the reference texts' silkscreen location as necessary.

#### Export from Kicad, order from JLCPCB

Install [this](https://github.com/Bouni/kicad-jlcpcb-tools) plugin in Kicad to manage your components from LCSC and generate your Gerbers, BOM, and CPL. 

Upload your design to JLCPCB and order it:

## Conclusion

We've now successfully designed a PCB using JITX. You can use this as a reference project, copying this workflow to design your own systems. To learn more, check out the other recipes in [the JITX Cookbook Recipes repo](https://github.com/JITx-Inc/jitx-cookbook) and read through the [tutorials](https://docs.jitx.com/tutorials/index.html) in the JITX docs.

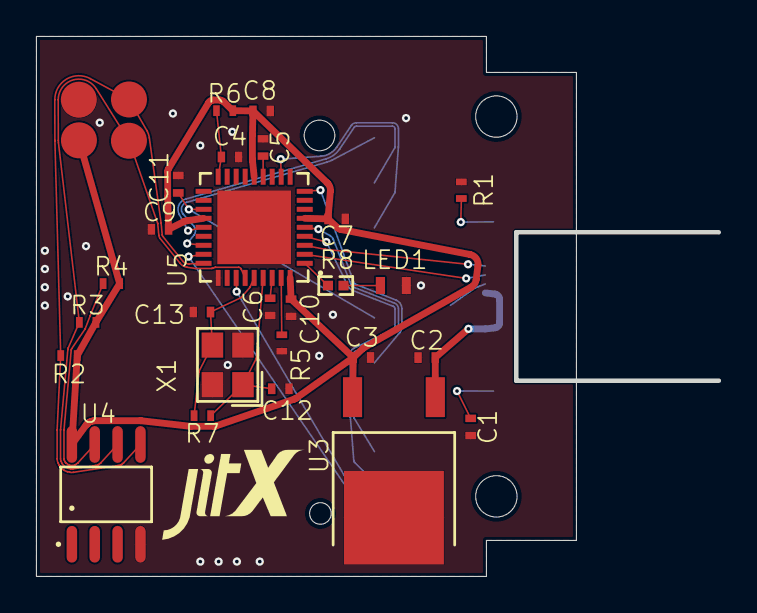
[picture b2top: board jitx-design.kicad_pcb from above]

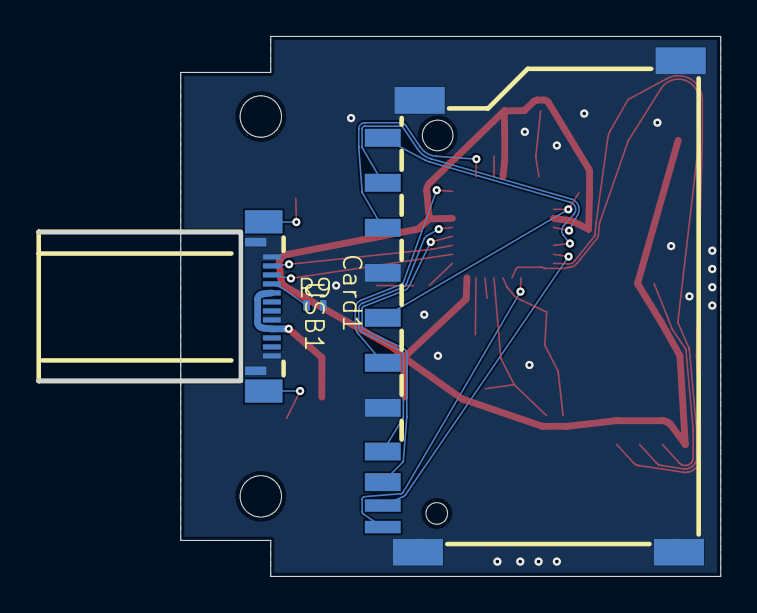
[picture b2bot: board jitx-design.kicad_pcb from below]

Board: 2 copper layers, 30.0 x 30.0 mm, 36 parts (3 on the bottom side), 28 nets.

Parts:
C1, C2, C3: 100n; Pkg0402_4
C4, C5, C6, C7, C8, C9, C10: 1u; Pkg0402_4
C11: 4.7u; Pkg0402_1
C12, C13: 27p; Pkg0402_4
Card1: SD-101; SD_SMD_SD_101
JITX1: non-BOM; JITX_SM_LP
LED1: 19-21/R6C-FP1Q2L/3T; Pkg0603
R1: 100K; Pkg0402
R2, R3, R4: 5K; Pkg0402
R5: 12K; Pkg0402_3
R6: 10K; Pkg0402_2
R7: 1M; Pkg0402
R8: 100R; R0402
R9: 5K1; Pkg0402
U1, U2: NPTH
U3: BD433M5FP-CE2; TO_252_3_L6_5_W5_8_P4_58_BR
U4: M24C04-WMN6TP; SOIC_8_L4_9_W3_9_P1_27_LS6_0_BL
U5: USB2240-AEZG-06; QFN_36_L6_0_W6_0_P0_50_TL_EP4_1
U6, U7, U8, U9: TESTPAD
USB1: TYPE-C-31-G-03; USB_C_SMD_TYPE_C_31_G_03
X1: 7B024000Q01; CRYSTAL_SMD_4P_L3_2_W2_5_BL

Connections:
unnamed: Card1.10 (CD), U5.26 (SD_nCD)
unnamed: Card1.1 (CD_DAT3), U5.23 (xD_D6_SD_D3_MS_D3)
unnamed: Card1.5 (CLK), U5.9 (xD_nWP_SD_CLK_MS_BS)
unnamed: Card1.2 (CMD), U5.11 (xD_CLE_SD_CMD_MS_D0)
unnamed: Card1.7 (DAT0), U5.5 (xD_D2_SD_D0_MS_D4)
unnamed: Card1.8 (DAT1), U5.4 (xD_D3_SD_D1_MS_D5)
unnamed: Card1.9 (DAT2), U5.25 (xD_D5_SD_D2)
unnamed: C11.2, Card1.4 (VDD), U5.21 (CRD_PWR)
unnamed: Card1.11 (WP), U5.30 (xD_D4_SD_WP_MS_SCLK)
unnamed: LED1.1 (a), R8.2
unnamed: R4.1, U4.7 (WC_NOT)
unnamed: R8.1, U5.1 (LED)
unnamed: R5.1, U5.35 (RBIAS)
unnamed: C4.2, R6.1, U5.18 (RESET_N)
unnamed: C5.2, U5.13 (VDD18)
unnamed: C6.2, U5.34 (VDD18PLL)
unnamed: C12.1, R7.1, U5.33 (XTAL1_CLKIN), X1.1 (IN)
unnamed: C13.1, R7.2, U5.32 (XTAL2), X1.3 (OUT)
unnamed: R9.1, USB1.A5 (CC1)
unnamed: R1.2, USB1.14 (GND0)
unnamed: C1.1, USB1.15 (GND2)
RXD_SDA: R2.1, U4.5 (SDA), U5.27 (RXD_SDA), U8.tp (p)
TXD_SCK_MS_SKT_SEL: R3.1, U4.6 (SCL), U5.31 (TXD_SCK_MS_SKT_SEL), U9.tp (p)
USB+: U5.2 (USB+), USB1.A6 (DP1)
USB-: U5.3 (USB-), USB1.A7 (DN1)
gnd: C1.2, C2.1, C3.1, C4.1, C5.1, C6.1, C7.1, C8.1, C9.1, C10.1, C11.1, C12.2, C13.2, Card1.3 (VSS1), Card1.6 (VSS2), Card1.12 (SHELL0), Card1.13 (SHELL1), Card1.14 (SHELL2), Card1.15 (SHELL3), LED1.2 (c), R1.1, R5.2, R9.2, U3.2 (FIN), U4.4 (VSS), U5.28 (TEST), U5.37 (GND), U7.tp (p), USB1.13 (GND1), USB1.16 (GND3), USB1.A1 (GND6), USB1.A12 (GND5), USB1.B12 (GND4), X1.2 (GND0), X1.4 (GND1)
vdd33: C3.2, C7.2, C8.2, C9.2, C10.2, R2.2, R3.2, R4.2, R6.2, U3.3 (VOUT), U4.8 (VCC), U5.6 (VDD330), U5.14 (VDD331), U5.22 (VDD332), U5.36 (VDDA33), U6.tp (p)
vdd50: C2.2, U3.1 (VCC), USB1.A4 (VBUS1), USB1.B9 (VBUS0)
